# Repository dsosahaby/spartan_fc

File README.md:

# spartan_fc

Quadcopter flight controller hardware for betaflight firmware

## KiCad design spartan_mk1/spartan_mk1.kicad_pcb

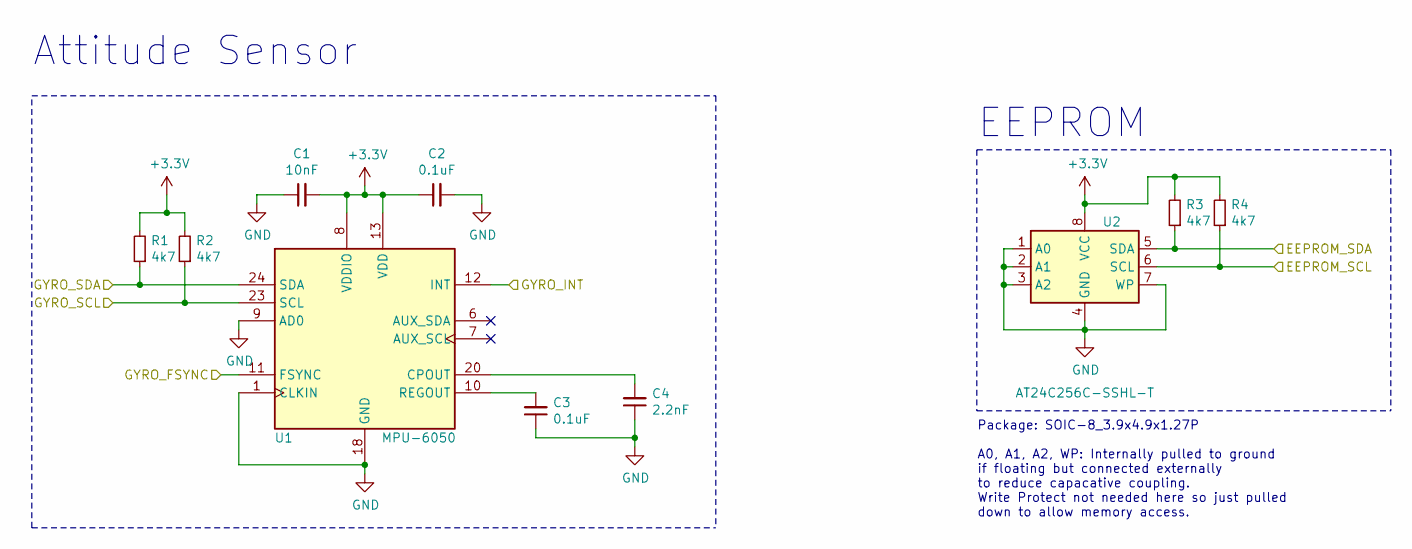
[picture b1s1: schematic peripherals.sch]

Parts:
C1: 10nF; C_0402_1005Metric
C2, C3: 0.1uF; C_0402_1005Metric
C4: 2.2nF; C_0402_1005Metric
R1, R2, R3, R4: 4k7; R_0402_1005Metric
U1: MPU-6050; InvenSense_QFN-24_4x4mm_P0.5mm
U2: AT24C256C-SSHL-T; SOIC-8_3.9x4.9mm_P1.27mm

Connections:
+3V3: C1.2, C2.1, R1.2, R2.2, R3.2, R4.2, U1.8 (VDDIO), U1.13 (VDD), U2.8 (VCC); also elsewhere on the board
/EEPROM_SCL: R4.1, U2.6 (SCL); also elsewhere on the board
/EEPROM_SDA: R3.1, U2.5 (SDA); also elsewhere on the board
/GYRO_FSYNC: U1.11 (FSYNC); also elsewhere on the board
/GYRO_INT: U1.12 (INT); also elsewhere on the board
/GYRO_SCL: R2.1, U1.23 (SCL); also elsewhere on the board
/GYRO_SDA: R1.1, U1.24 (SDA); also elsewhere on the board
GND: C1.1, C2.2, C3.1, C4.1, U1.1 (CLKIN), U1.9 (AD0), U1.18 (GND), U2.1 (A0), U2.2 (A1), U2.3 (A2), U2.4 (GND), U2.7 (WP); also elsewhere on the board
unnamed: C3.2, U1.10 (REGOUT)
unnamed: C4.2, U1.20 (CPOUT)

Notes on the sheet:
Attitude Sensor
EEPROM
Package: SOIC-8_3.9x4.9x1.27P A0, A1, A2, WP: Internally pulled to ground if floating but connected externally to reduce capacative coupling. Write Protect not needed here so just pulled down to allow memory access.

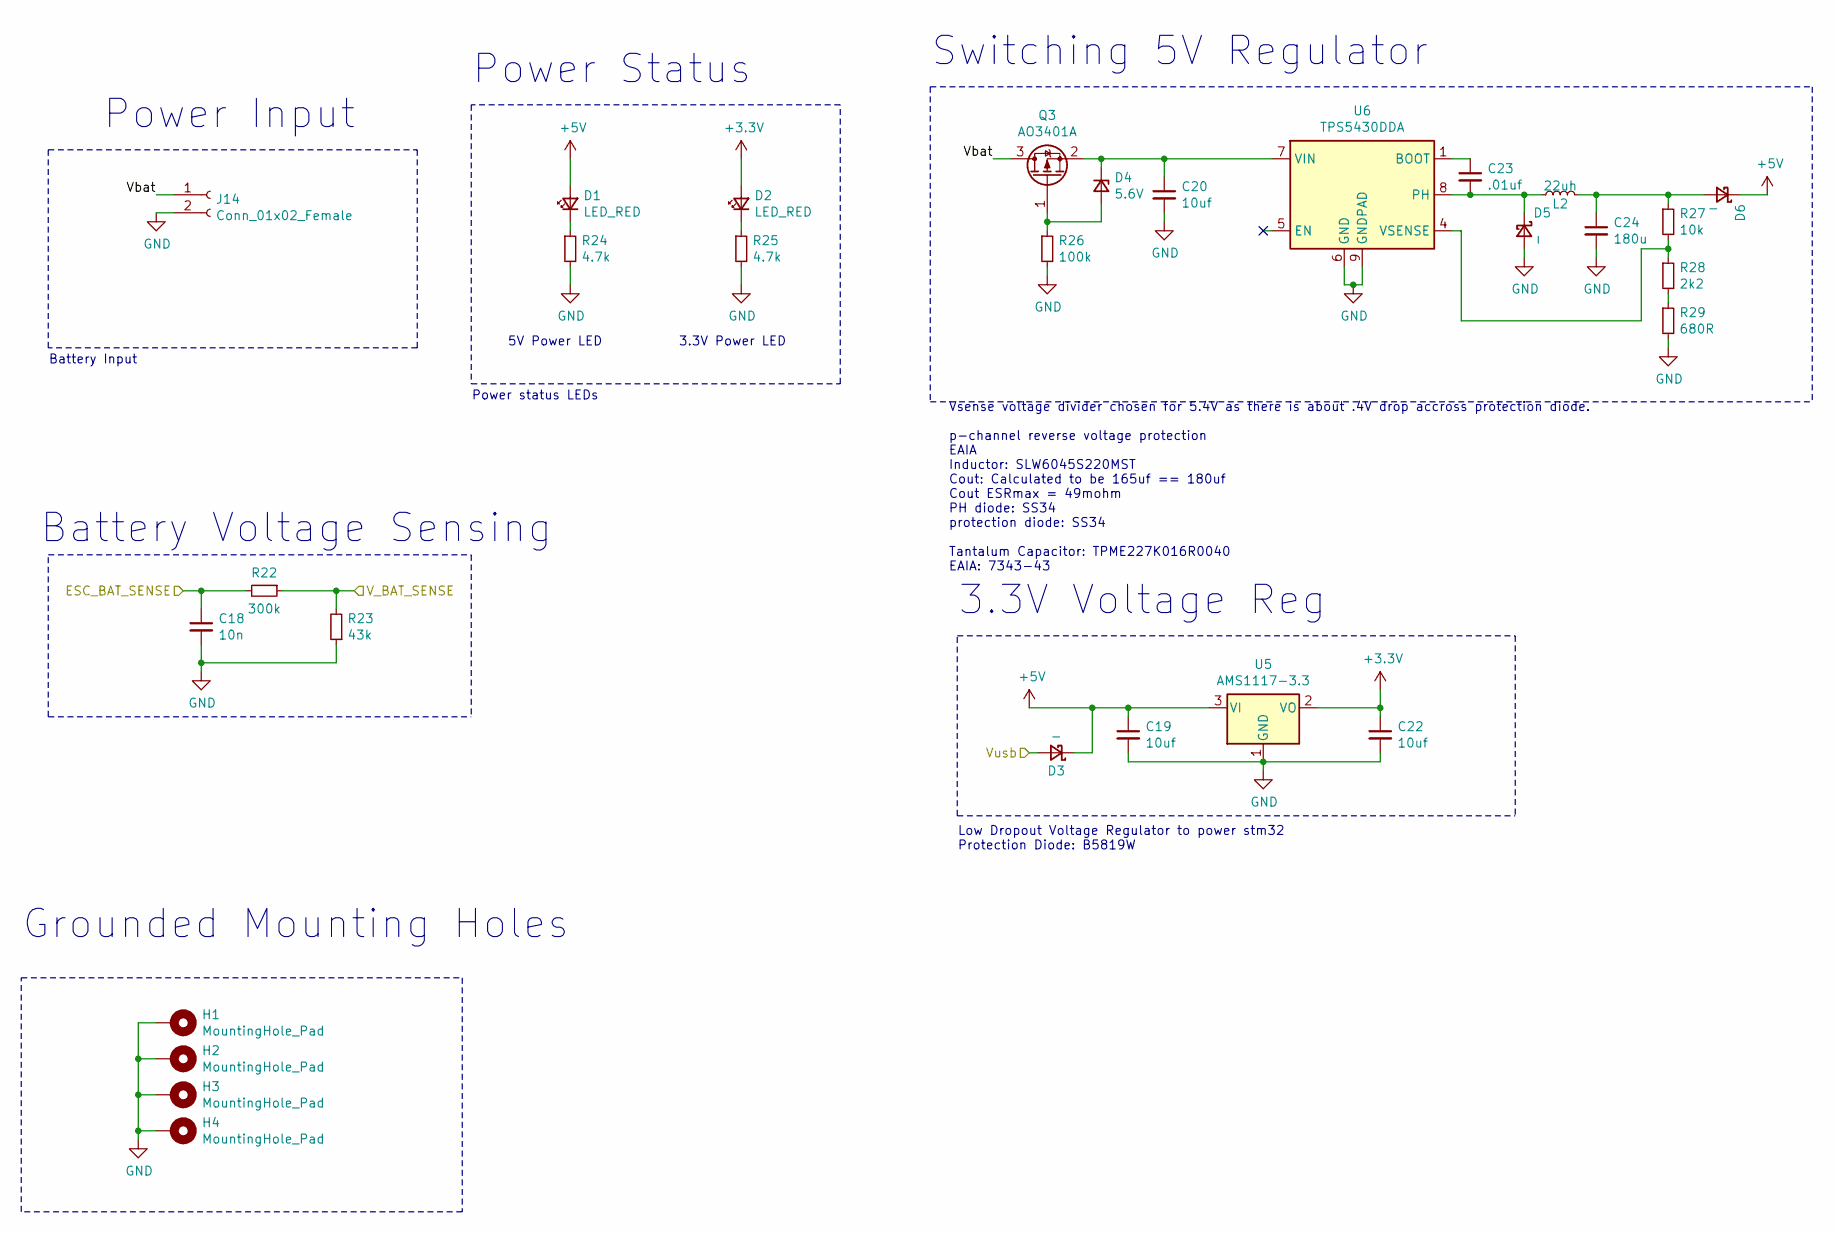
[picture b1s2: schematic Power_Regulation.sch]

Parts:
C18: 10n; C_0603_1608Metric; LCSC Part # C57112
C19: 10uf; C_0805_2012Metric; LCSC Part # C15850
C20: 10uf; C_1206_3216Metric; LCSC Part # C13585
C22: 10uf; C_0603_1608Metric; LCSC Part # C19702
C23: .01uf; C_0402_1005Metric; LCSC Part # C15195
C24: 180u; CP_EIA-7343-43
D1, D2: LED_RED; LED_0603_1608Metric; LCSC Part # C2286
D3: _; D_SOD-123; LCSC Part # C8598
D4: 5.6V; D_MiniMELF; LCSC Part # C8062
D5, D6: _; D_SMA; LCSC Part # C8678
H1, H2, H3, H4: MountingHole_Pad; MountingHole_3.2mm_M3_Pad_Via
J14: Conn_01x02_Female; 01x02_3mm
L2: 22uh; SLW6045_6mmX6mm; LCSC Part # C206321
Q3: AO3401A; SOT-23; LCSC Part # C15127
R22: 300k; R_0603_1608Metric; LCSC Part # C23024
R23: 43k; R_0603_1608Metric; LCSC Part # C23172
R24, R25: 4.7k; R_0402_1005Metric; LCSC Part # C25900
R26: 100k; R_0805_2012Metric; LCSC Part # C17407
R27: 10k; R_0402_1005Metric; LCSC Part # C25744
R28: 2k2; R_0402_1005Metric; LCSC Part # C25879
R29: 680R; R_0402_1005Metric; LCSC Part # C25130
U5: AMS1117-3.3; SOT-223-3_TabPin2; LCSC Part # C6186
U6: TPS5430DDA; TI_SO-PowerPAD-8_ThermalVias; LCSC Part # C9864

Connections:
+3V3: C22.1, D2.2 (A), U5.2 (VO); also elsewhere on the board
+5V: C19.1, D1.2 (A), D3.1 (K), D6.1 (K), U5.3 (VI); also elsewhere on the board
/ESC_BAT_SENSE: C18.1, R22.2; also elsewhere on the board
/Power_Regulation/Vbat: J14.1, Q3.3 (D)
/V_BAT_SENSE: R22.1, R23.2; also elsewhere on the board
/V_USB: D3.2 (A); also elsewhere on the board
GND: C18.2, C19.2, C20.2, C22.2, C24.2, D5.2 (A), H1.1, H2.1, H3.1, H4.1, J14.2, R23.1, R24.2, R25.2, R26.2, R29.2, U5.1 (GND), U6.6 (GND), U6.9 (GNDPAD); also elsewhere on the board
unnamed: C20.1, D4.1 (K), Q3.2 (S), U6.7 (VIN)
unnamed: C23.1, U6.1 (BOOT)
unnamed: C23.2, D5.1 (K), L2.1, U6.8 (PH)
unnamed: C24.1, D6.2 (A), L2.2, R27.1
unnamed: D1.1 (K), R24.1
unnamed: D2.1 (K), R25.1
unnamed: D4.2 (A), Q3.1 (G), R26.1
unnamed: R27.2, R28.1, U6.4 (VSENSE)
unnamed: R28.2, R29.1

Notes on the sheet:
Battery Input
Low Dropout Voltage Regulator to power stm32 Protection Diode: B5819W
Vsense voltage divider chosen for 5.4V as there is about .4V drop accross protection diode. p-channel reverse voltage protection EAIA Inductor: SLW6045S220MST Cout: Calculated to be 165uf == 180uf Cout ESRmax = 49mohm PH diode: SS34 protection diode: SS34 Tantalum Capacitor: TPME227K016R0040 EAIA: 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
3.3V Power LED
5V Power LED
Power status LEDs
Switching 5V Regulator
3.3V Voltage Reg
Power Input
Power Status
Battery Voltage Sensing
Grounded Mounting Holes

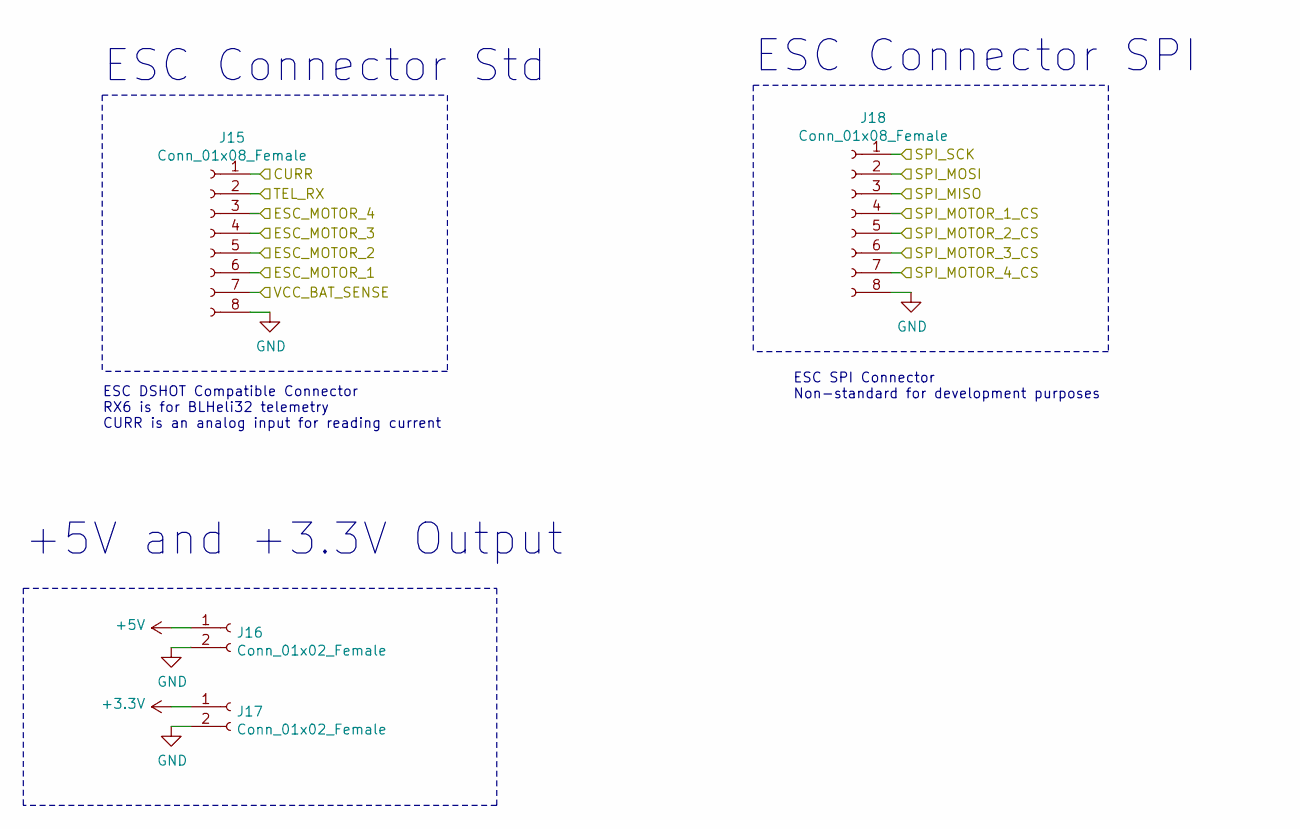
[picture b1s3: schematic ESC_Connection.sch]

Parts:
J15, J18: Conn_01x08_Female; JST_SH_BM08B-SRSS-TB_1x08-1MP_P1.00mm_Vertical
J16, J17: Conn_01x02_Female; PinHeader_1x02_P2.54mm_Vertical

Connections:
/CURR_SENSE: J15.1; also elsewhere on the board
/ESC_1_CS: J18.4; also elsewhere on the board
/ESC_2_CS: J18.5; also elsewhere on the board
/ESC_3_CS: J18.6; also elsewhere on the board
/ESC_4_CS: J18.7; also elsewhere on the board
/ESC_BAT_SENSE: J15.7; also elsewhere on the board
/ESC_DSHOT_1: J15.6; also elsewhere on the board
/ESC_DSHOT_2: J15.5; also elsewhere on the board
/ESC_DSHOT_3: J15.4; also elsewhere on the board
/ESC_DSHOT_4: J15.3; also elsewhere on the board
/SPI_ESC_MISO: J18.3; also elsewhere on the board
/SPI_ESC_MOSI: J18.2; also elsewhere on the board
/SPI_ESC_SCK: J18.1; also elsewhere on the board
/UART3_RX: J15.2; also elsewhere on the board
GND: J15.8, J16.2, J17.2, J18.8; also elsewhere on the board

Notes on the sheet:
ESC DSHOT Compatible Connector RX6 is for BLHeli32 telemetry CURR is an analog input for reading current
ESC Connector Std
ESC Connector SPI
ESC SPI Connector Non-standard for development purposes
+5V and +3.3V Output

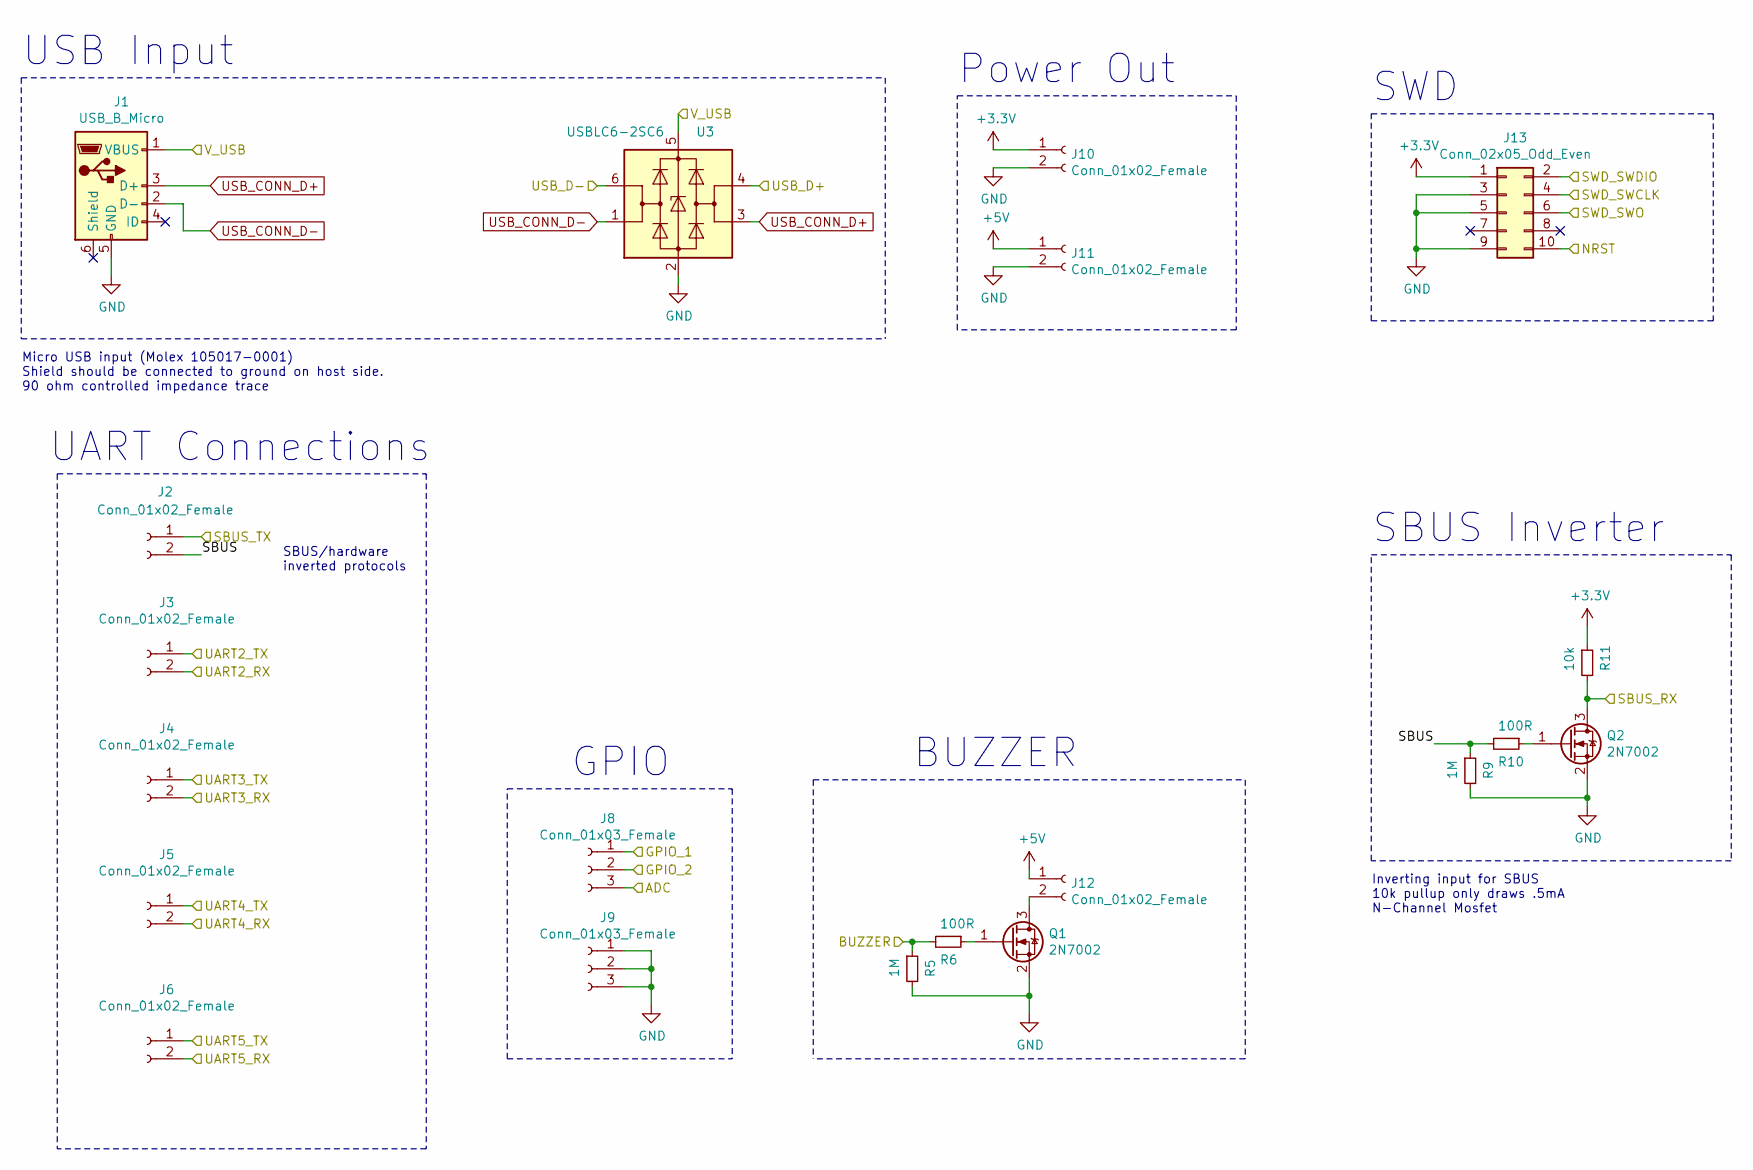
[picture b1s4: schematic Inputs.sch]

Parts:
J1: USB_B_Micro; USB_Micro-B_Molex-105017-0001
J2, J3, J4, J5, J6, J10, J12: Conn_01x02_Female; 01x02_1.5mm
J8, J9: Conn_01x03_Female; 01x03_1.5mm
J11: Conn_01x02_Female; 01x02_3mm
J13: Conn_02x05_Odd_Even; PinHeader_2x05_P1.27mm_Vertical_SMD
Q1, Q2: 2N7002; SOT-23; LCSC Part # C8545
R5, R9: 1M; R_0402_1005Metric; LCSC Part # C26083
R6, R10: 100R; R_0805_2012Metric; LCSC Part # C17408
R11: 10k; R_0402_1005Metric; LCSC Part # C25744
U3: USBLC6-2SC6; SOT-23-6; LCSC Part # C7519

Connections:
+3V3: J10.1, J13.1, R11.1; also elsewhere on the board
+5V: J11.1, J12.1; also elsewhere on the board
/BUZZER: R5.1, R6.2; also elsewhere on the board
/GEN_ADC: J8.3; also elsewhere on the board
/GPIO_1: J8.1; also elsewhere on the board
/GPIO_2: J8.2; also elsewhere on the board
/Inputs/SBUS: J2.2, R9.1, R10.2
/NRST: J13.10; also elsewhere on the board
/SBUS_RX: Q2.3 (D), R11.2; also elsewhere on the board
/SBUS_TX: J2.1; also elsewhere on the board
/SWCLK: J13.4; also elsewhere on the board
/SWDIO: J13.2; also elsewhere on the board
/SWO: J13.6; also elsewhere on the board
/UART2_RX: J3.2; also elsewhere on the board
/UART2_TX: J3.1; also elsewhere on the board
/UART3_RX: J4.2; also elsewhere on the board
/UART3_TX: J4.1; also elsewhere on the board
/UART4_RX: J5.2; also elsewhere on the board
/UART4_TX: J5.1; also elsewhere on the board
/UART5_RX: J6.2; also elsewhere on the board
/UART5_TX: J6.1; also elsewhere on the board
/USB_D+: U3.4 (I/O2); also elsewhere on the board
/USB_D-: U3.6 (I/O1); also elsewhere on the board
/V_USB: J1.1 (VBUS), U3.5 (VBUS); also elsewhere on the board
GND: J1.5 (GND), J9.1, J9.2, J9.3, J10.2, J11.2, J13.3, J13.5, J13.9, Q1.2 (S), Q2.2 (S), R5.2, R9.2, U3.2 (GND); also elsewhere on the board
unnamed: J12.2, Q1.3 (D)
unnamed: Q1.1 (G), R6.1
unnamed: Q2.1 (G), R10.1
USB_CONN_D+: J1.3 (D+), U3.3 (I/O2)
USB_CONN_D-: J1.2 (D-), U3.1 (I/O1)

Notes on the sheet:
Micro USB input (Molex 105017-0001) Shield should be connected to ground on host side. 90 ohm controlled impedance trace
Inverting input for SBUS 10k pullup only draws .5mA N-Channel Mosfet
SBUS Inverter
USB Input
SBUS/hardware inverted protocols
UART Connections
GPIO
Power Out
SWD
BUZZER

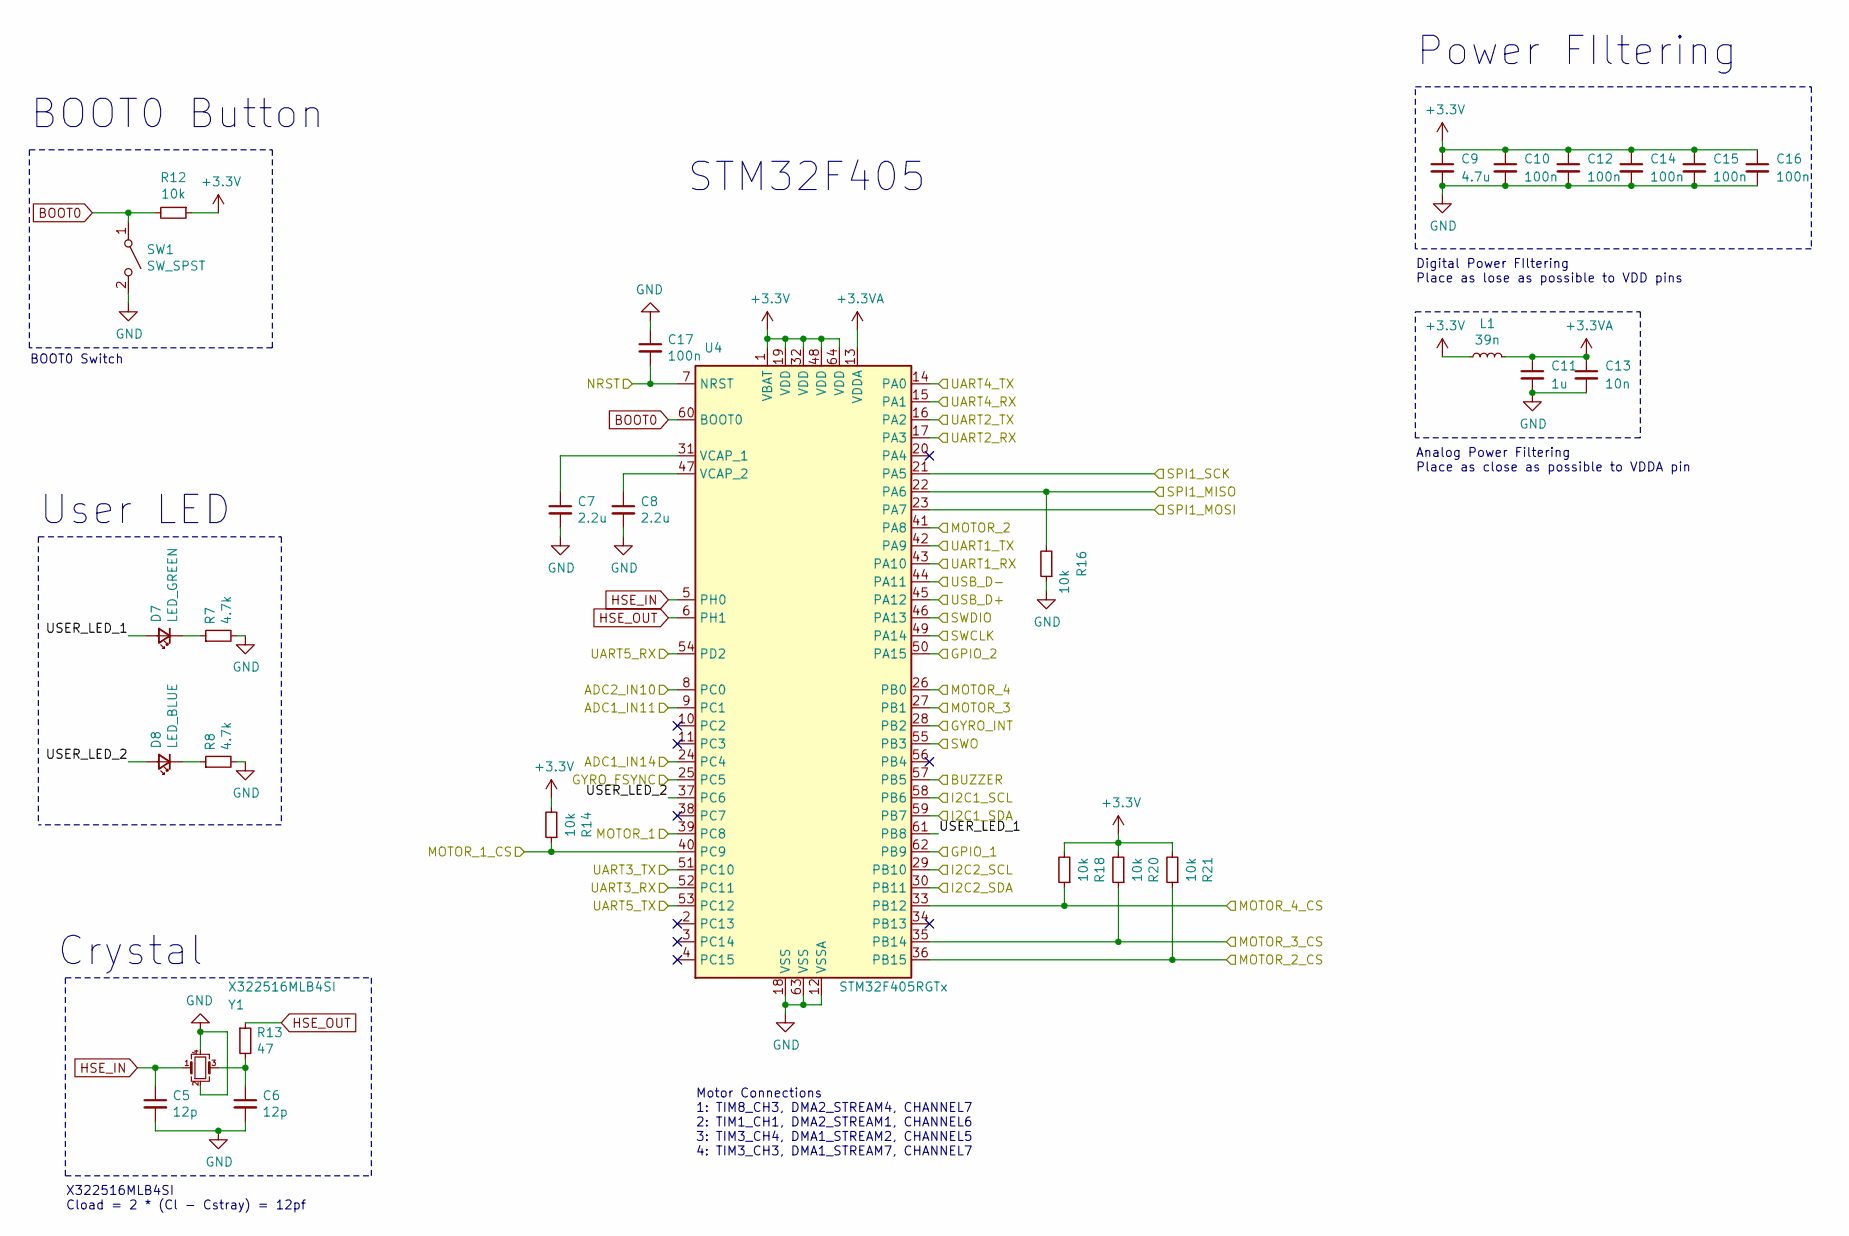
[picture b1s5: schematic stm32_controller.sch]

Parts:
C5, C6: 12p; C_0402_1005Metric; LCSC Part # C1547
C7, C8: 2.2u; C_0603_1608Metric; LCSC Part # C12530
C9: 4.7u; C_0402_1005Metric; LCSC Part # C23733
C10, C12, C14, C15, C16, C17: 100n; C_0402_1005Metric; LCSC Part # C1525
C11: 1u; C_0402_1005Metric; LCSC Part # C52923
C13: 10n; C_0402_1005Metric; LCSC Part # C15195
D7: LED_GREEN; LED_0603_1608Metric; LCSC Part # C205443
D8: LED_BLUE; LED_0603_1608Metric; LCSC Part # C72041
L1: 39n; L_0402_1005Metric; LCSC Part # C18830
R7, R8: 4.7k; R_0402_1005Metric; LCSC Part # C25900
R12, R14, R16, R18, R20, R21: 10k; R_0402_1005Metric; LCSC Part # C25744
R13: 47; R_0402_1005Metric; LCSC Part # C25118
SW1: SW_SPST; SW_B3U-3000P
U4: STM32F405RGTx; LQFP-64_10x10mm_P0.5mm; LCSC Part # C15742
Y1: X322516MLB4SI; Crystal_SMD_3225-4Pin_3.2x2.5mm; LCSC Part # C13738

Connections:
+3.3VA: C11.1, C13.1, L1.2, U4.13 (VDDA)
+3V3: C9.1, C10.1, C12.1, C14.1, C15.1, C16.1, L1.1, R12.1, R14.2, R18.2, R20.2, R21.2, U4.1 (VBAT), U4.19 (VDD), U4.32 (VDD), U4.48 (VDD), U4.64 (VDD); also elsewhere on the board
/BUZZER: U4.57 (PB5); also elsewhere on the board
/CURR_SENSE: U4.8 (PC0); also elsewhere on the board
/EEPROM_SCL: U4.29 (PB10); also elsewhere on the board
/EEPROM_SDA: U4.30 (PB11); also elsewhere on the board
/ESC_1_CS: R14.1, U4.40 (PC9); also elsewhere on the board
/ESC_2_CS: R21.1, U4.36 (PB15); also elsewhere on the board
/ESC_3_CS: R20.1, U4.35 (PB14); also elsewhere on the board
/ESC_4_CS: R18.1, U4.33 (PB12); also elsewhere on the board
/ESC_DSHOT_1: U4.39 (PC8); also elsewhere on the board
/ESC_DSHOT_2: U4.41 (PA8); also elsewhere on the board
/ESC_DSHOT_3: U4.27 (PB1); also elsewhere on the board
/ESC_DSHOT_4: U4.26 (PB0); also elsewhere on the board
/GEN_ADC: U4.9 (PC1); also elsewhere on the board
/GPIO_1: U4.62 (PB9); also elsewhere on the board
/GPIO_2: U4.50 (PA15); also elsewhere on the board
/GYRO_FSYNC: U4.25 (PC5); also elsewhere on the board
/GYRO_INT: U4.28 (PB2); also elsewhere on the board
/GYRO_SCL: U4.58 (PB6); also elsewhere on the board
/GYRO_SDA: U4.59 (PB7); also elsewhere on the board
/NRST: C17.2, U4.7 (NRST); also elsewhere on the board
/SBUS_RX: U4.42 (PA9); also elsewhere on the board
/SBUS_TX: U4.43 (PA10); also elsewhere on the board
/SPI_ESC_MISO: R16.2, U4.22 (PA6); also elsewhere on the board
/SPI_ESC_MOSI: U4.23 (PA7); also elsewhere on the board
/SPI_ESC_SCK: U4.21 (PA5); also elsewhere on the board
/STM32 Controller/USER_LED_1: D7.2 (A), U4.61 (PB8)
/STM32 Controller/USER_LED_2: D8.2 (A), U4.37 (PC6)
/SWCLK: U4.49 (PA14); also elsewhere on the board
/SWDIO: U4.46 (PA13); also elsewhere on the board
/SWO: U4.55 (PB3); also elsewhere on the board
/UART2_RX: U4.17 (PA3); also elsewhere on the board
/UART2_TX: U4.16 (PA2); also elsewhere on the board
/UART3_RX: U4.52 (PC11); also elsewhere on the board
/UART3_TX: U4.51 (PC10); also elsewhere on the board
/UART4_RX: U4.15 (PA1); also elsewhere on the board
/UART4_TX: U4.14 (PA0); also elsewhere on the board
/UART5_RX: U4.53 (PC12); also elsewhere on the board
/UART5_TX: U4.54 (PD2); also elsewhere on the board
/USB_D+: U4.45 (PA12); also elsewhere on the board
/USB_D-: U4.44 (PA11); also elsewhere on the board
/V_BAT_SENSE: U4.24 (PC4); also elsewhere on the board
BOOT0: R12.2, SW1.1 (A), U4.60 (BOOT0)
GND: C5.2, C6.2, C7.2, C8.2, C9.2, C10.2, C11.2, C12.2, C13.2, C14.2, C15.2, C16.2, C17.1, R7.2, R8.2, R16.1, SW1.2 (B), U4.12 (VSSA), U4.18 (VSS), U4.63 (VSS), Y1.2, Y1.4; also elsewhere on the board
HSE_IN: C5.1, U4.5 (PH0), Y1.1
HSE_OUT: R13.1, U4.6 (PH1)
unnamed: C6.1, R13.2, Y1.3
unnamed: C7.1, U4.31 (VCAP_1)
unnamed: C8.1, U4.47 (VCAP_2)
unnamed: D7.1 (K), R7.1
unnamed: D8.1 (K), R8.1

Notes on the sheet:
X322516MLB4SI Cload = 2 * (Cl - Cstray) = 12pf
BOOT0 Switch
Digital Power FIltering Place as lose as possible to VDD pins
Analog Power Filtering Place as close as possible to VDDA pin
Power FIltering
Crystal
BOOT0 Button
STM32F405
Motor Connections 1: TIM8_CH3, DMA2_STREAM4, CHANNEL7 2: TIM1_CH1, DMA2_STREAM1, CHANNEL6 3: TIM3_CH4, DMA1_STREAM2, CHANNEL5 4: TIM3_CH3, DMA1_STREAM7, CHANNEL7
User LED

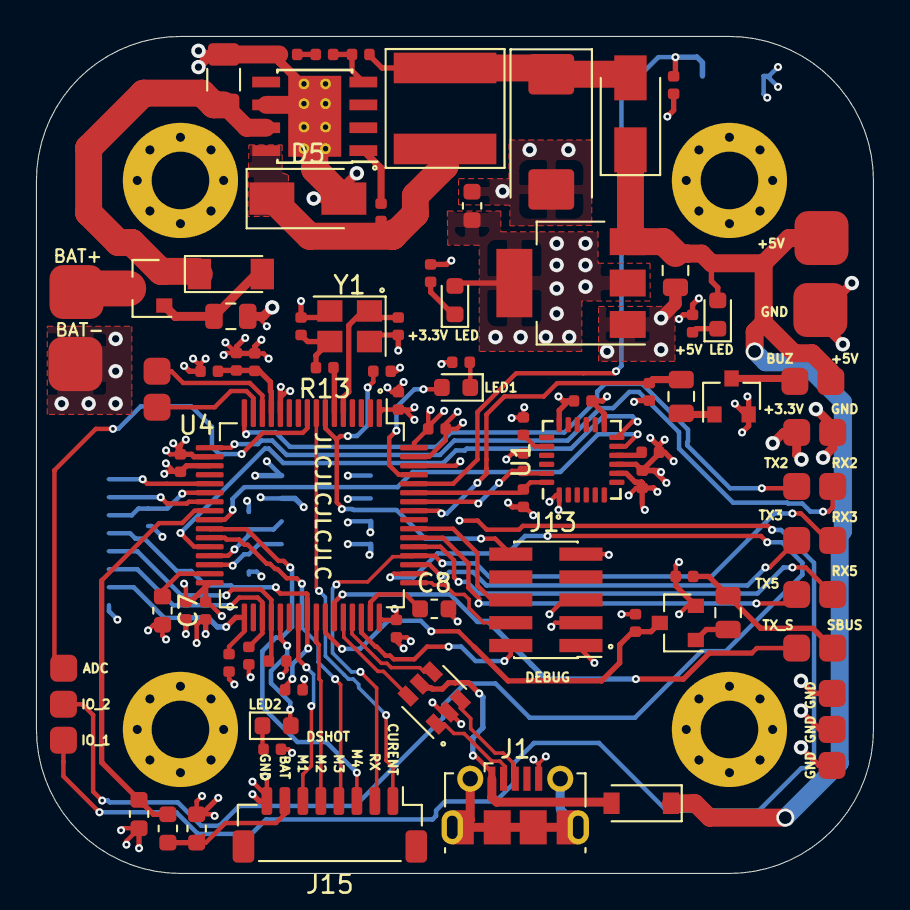
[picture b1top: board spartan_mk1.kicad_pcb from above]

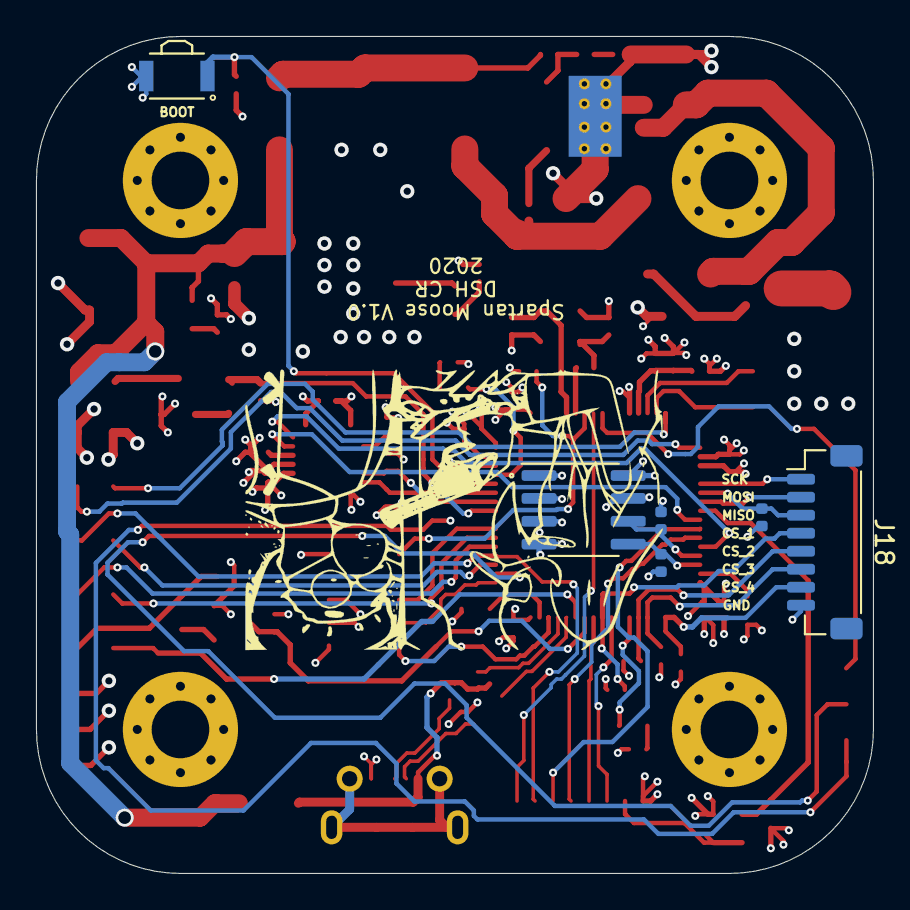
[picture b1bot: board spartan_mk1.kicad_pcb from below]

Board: 4 copper layers, 46.5 x 46.5 mm, 89 parts (6 on the bottom side), 73 nets.

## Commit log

2020-10-18 added main pcb design
2020-10-19 Added git ignore
2020-10-19 Added ESC connectors in schematic
2020-10-19 Added TODO
2020-10-24 Complete schematic with DRC done
2020-10-26 Footprints added started PCB placement
2020-10-28 Changed offboard connections to SMD pads for space
2020-10-30 Almost complete PCB layout (no routing)
2020-11-01 updated placement
2020-11-02 Routing in progress
2020-11-02 Almost complete routing
2020-11-03 Updated routing. ALMOST done
2020-11-04 Improved grounding vias and fixed filter capacitor ground routing
2020-11-04 _routing
2020-11-05 Routing complete. Passed DRC
2020-11-07 Routing complete. Labels complete
2020-11-07 Updated LED labels
2020-11-09 Generated gerber files. Positions and BOM assemly files generated
2020-11-09 Complete assembly and gerber. Small rotational errors in position file
